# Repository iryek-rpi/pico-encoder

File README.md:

# TCP/IP packet encoder based on Raspberry Pi Pico W + W5500-EVB-Pico

* Raspberry Pi Pico W for serving a device configuration web page
* W5500-EVB-Pico from Wiznet for TCP/IP relay

## Sponsorship from PCBWay

* [PCBWay](https://www.pcbway.com/) kindly provided PCB of this device. This is my first time using the company's service.
* My honest impression is that their service is **well-streamlined with web-based ordering process** with good support of **instant chat assistance**. I could quickly make my order on the comprehensive web page.
* It took about a week to receive the assembled PCB at home in Korea. It was good to see that **each PCB was separately packaged**. The quality of the final product was excellent.
* I want to thank PCBWay again for their support. Highly recommend PCBWay. Try their excellent service at https://www.pcbway.com/ .

### Package arrived!
  * 
  * 
  * 

### KiCad schematics & pcb
  * 
  * 
### FreeCAD design & enclosure
  * 
  * 
  *

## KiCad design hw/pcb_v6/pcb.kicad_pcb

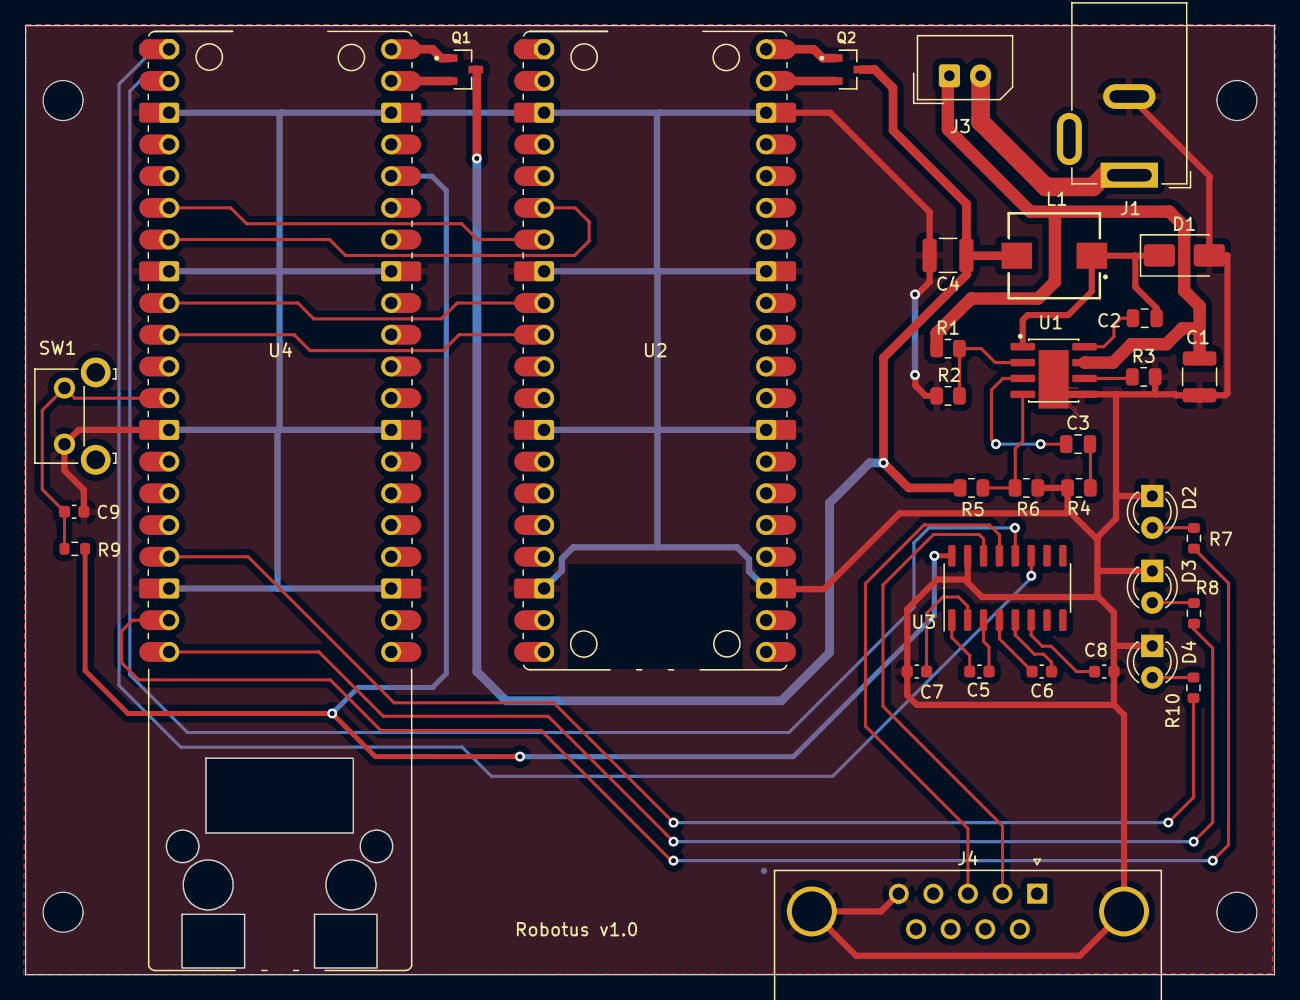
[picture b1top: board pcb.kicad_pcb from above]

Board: 2 copper layers, 100.0 x 76.0 mm, 34 parts (0 on the bottom side), 37 nets.

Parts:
C1: 10uF 50V; C_1210_3225Metric
C2: 0.1uF; C_0805_2012Metric
C3: 220pF; C_0805_2012Metric
C4: 22uF; C_1210_3225Metric
C5, C6, C7, C8: 100nF; C_0603_1608Metric
C9: 10nF; C_0603_1608Metric
D1: SS34; D_SMA
D2, D3, D4: LED; LED_D3.0mm
J1: Barrel_Jack_MountingPin; BarrelJack_GCT_DCJ200-10-A_Horizontal
J3: Conn_01x02; Molex_SPOX_5267-02A_1x02_P2.50mm_Vertical
J4: RS232; DSUB-9_Female_Horizontal_P2.77x2.84mm_EdgePinOffset7.70mm_H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
L1: 4.7uH; INDP7368X320_Inductor
Q1, Q2: DMG2305UX-7; SOT91P240X110-3N_DMG2305UX-7
R1: 100K; R_0805_2012Metric
R2: 24K9; R_0805_2012Metric
R3: 200K; R_0805_2012Metric
R4: 68K; R_0805_2012Metric
R5: 43K; R_0805_2012Metric
R6: 8K2; R_0805_2012Metric
R7, R8, R10: 120; R_0603_1608Metric
R9: 1K; R_0603_1608Metric
SW1: SW_Push; SW_SPST_Omron_B3F-315x_Angled
U1: MP1584EN; SOIC127P600X170-9N_MP1584EN
U2: Raspberry Pi Pico W; Raspberry_Pi_Pico_W_SMT_THT
U3: MAX3232; SO-16_3.9x9.9mm_P1.27mm
U4: W5500-EVB-Pico; W5500-EVB-Pico_SMT_THT

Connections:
+3.3V: R9.1, U3.16 (VCC), U4.36 (3V3)
+5V: C4.1, L1.2, Q1.3, Q2.3, R5.1
+24V: C1.1, J3.1, R1.1, U1.7 (VIN)
+24VP: J1.1, J3.2
BTN: C9.1, R9.2, SW1.2, U4.12 (GPIO9)
GND: C1.2, C4.2, C7.2, C8.2, C9.2, D1.2, D2.1 (K), D3.1 (K), D4.1 (K), J1.2, J4.0 (PAD), J4.5, R2.2, R3.2, R4.2, R6.2, SW1.1, U1.5 (GND), U2.3 (GND_1), U2.8 (GND_2), U2.13 (GND_3), U2.18 (GND_4), U2.23 (GND_5), U2.28 (GND_6), U2.33 (AGND), U2.38 (GND_7), U3.15 (GND), U4.3 (GND_1), U4.8 (GND_2), U4.13 (GND_3), U4.18 (GND_4), U4.23 (GND_5), U4.28 (GND_6), U4.33 (AGND), U4.38 (GND_7)
unnamed: C3.2, R4.1
unnamed: D2.2 (A), R7.1
unnamed: D3.2 (A), R8.1
unnamed: D4.2 (A), R10.1
unnamed: C2.1, U1.8 (BST)
unnamed: C3.1, U1.3 (COMP)
unnamed: R1.2, R2.1, U1.2 (EN)
unnamed: R5.2, R6.1, U1.4 (FB)
unnamed: R3.1, U1.6 (FREQ)
unnamed: C2.2, L1.1, U1.1 (SW)
unnamed: Q2.1, U2.40 (VBUS)
unnamed: Q2.2, U2.39 (VSYS)
unnamed: C5.1, U3.1 (C1+)
unnamed: C5.2, U3.3 (C1-)
unnamed: C6.1, U3.4 (C2+)
unnamed: C6.2, U3.5 (C2-)
unnamed: C7.1, U3.2 (VS+)
unnamed: C8.1, U3.6 (VS-)
unnamed: R10.2, U4.17 (GPIO13)
unnamed: R7.2, U4.19 (GPIO14)
unnamed: R8.2, U4.20 (GPIO15)
unnamed: Q1.1, U4.40 (VBUS)
unnamed: Q1.2, U4.39 (VSYS)
P6: U2.9 (GPIO6), U4.9 (GPIO6)
P7: U2.10 (GPIO7), U4.10 (GPIO7)
RS232_RX: J4.3, U3.13 (R1IN)
RS232_TX: J4.2, U3.14 (T1OUT)
UART0_RX: U3.12 (R1OUT), U4.2 (GPIO1)
UART0_TX: U3.11 (T1IN), U4.1 (GPIO0)
UART1_RX: U2.6 (GPIO4), U4.7 (GPIO5)
UART1_TX: U2.7 (GPIO5), U4.6 (GPIO4)

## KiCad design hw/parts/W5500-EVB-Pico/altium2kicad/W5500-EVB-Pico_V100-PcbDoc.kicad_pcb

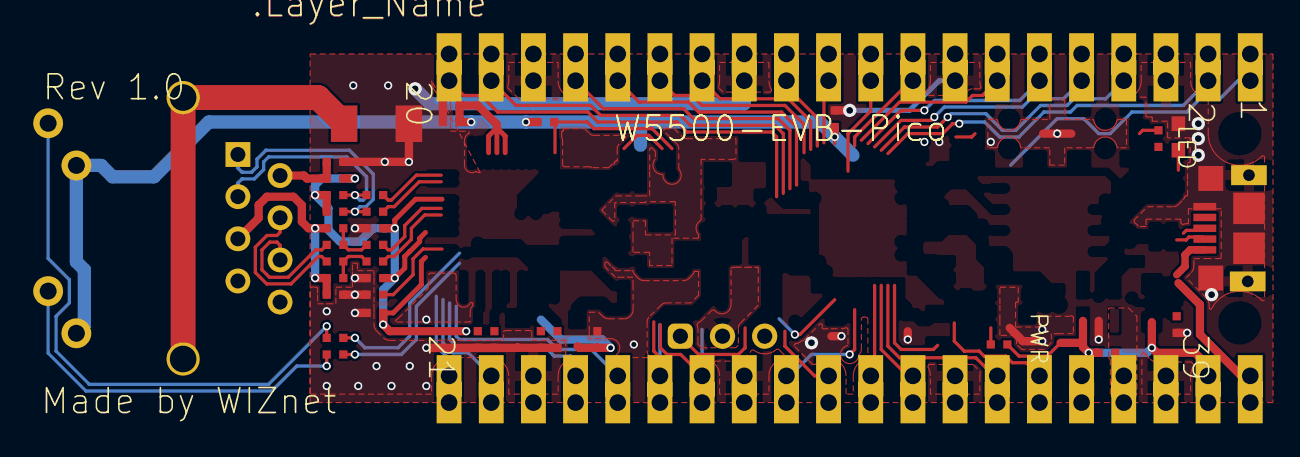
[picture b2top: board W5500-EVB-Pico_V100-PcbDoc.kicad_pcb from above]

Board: 2 copper layers, 39 parts (0 on the bottom side), 18 nets.

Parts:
C12, C15, C16, C17, C18, C19, C20, C21, C22, C23, C28, C29, C30, C35, C36: Ceramic CAP 0402(1005); CAP-0402
C31: Ceramic CAP 1808(4520); CAP-1808
J1, J2: 2.54mm 1x20 Pin Header DIP; IDC-1X20
J3: 2.54mm 1x3 Pin Header DIP; IDC-1X3
LD2: LED-0603; LED-0603-GREEN
P1: Micro USB B Connector SMD; MICRO 5P B DBX 6.4
P2: J1B1211CCD; RJ45-J1B1211CCD
R3, R4, R5, R12, R15, R16, R17, R18, R19, R20, R21, R22, R26, R27, R28, R29, R30: RES-0402

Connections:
3V3: C12.2, C15.2, C16.2, J2.16, P2.10, P2.12, R12.2
3V3A: C17.2, C18.2, C19.2, C20.2, C21.2, C22.2, C23.2, R19.2, R20.2, R28.1
3V3_EN: J2.17, R3.2
CHGND: C31.2, P2.S1, P2.S2
GND: C12.1, C15.1, C16.1, C17.1, C18.1, C19.1, C20.1, C21.1, C22.1, C23.1, C28.1, C29.1, C30.1, C31.1, J1.3, J1.8, J1.13, J1.18, J2.3, J2.8, J2.13, J2.18, J3.2, LD2.2, P1.5, P1.6, P1.7, P1.8, P1.9, P1.10, P1.11, R4.1, R27.2
GPIO20: J2.6, R12.1
NetC28_2: C28.2, P2.2, R28.2
NetC30_2: C30.2, P2.5, R21.1, R22.1
NetC35_1: C35.1, R18.1, R22.2
NetC35_2: C35.2, P2.4
NetC36_1: C36.1, R17.1, R21.2
NetC36_2: C36.2, P2.6
NetP2_1: P2.1, R16.1, R19.1
NetP2_3: P2.3, R15.1, R20.1
NetP2_9: P2.9, R29.1
NetP2_11: P2.11, R30.1
VBUS: J2.20, P1.1
VSYS: J2.19, R3.1, R5.2

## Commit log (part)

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2023-03-29 schematic v1 completed
2023-04-14 old pcb backups removed
2023-04-14 add pcbbackup/*.zip
2023-04-14 datasheets of parts used in JLCPCB 1st order
2023-04-14 bom xml for JLCPCB 1st order
2023-04-16 serial data example
2023-04-16 pico-w files
2023-04-16 backup ex files
2023-04-16 back up examples
2023-04-16 moved to memo folder
2023-04-17 저항 변경
2023-04-17 common read/write main.py for pico-w
2023-04-17 socket server client examples
2023-04-17 encryption
2023-04-17 w5500 successful receive / send
2023-04-25 case base for fitting pcb into the design
2023-04-25 latest kicad project files
2023-04-26 2023.4 최신 회로 및 PCB
2023-04-26 move to sw_pcbv1
2023-04-26 software for pcb v2
2023-04-27 json 예제
2023-04-27 setting
2023-04-28 uart1 settings exchange
2023-04-28 소자 이름 깨지는 거 수정
2023-04-28 소자 파일 이름 깨지는 문제 수정
2023-04-29 pico-w micropython release v1.20.0 2023.04.26
2023-04-29 None to 'N' in json
2023-04-29 main.py update
2023-04-29 phew example
2023-04-30 backup phew apis
2023-04-30 settings based on phewap
2023-05-06 firmwares
2023-05-06 example tcp code
2023-05-06 code for pcb v2
2023-05-06 new case design
2023-05-06 old pcb removed
2023-05-06 old pcb folder renamed
2023-05-06 2023.4 delivery from interboard
2023-05-06 pcb v6 a new copy for three LEDs
2023-05-06 refactor
2023-05-06 add comment
2023-05-06 sch update
2023-05-07 pcb update
2023-05-07 pcb backups
2023-05-07 power ic MP1584EN library footprint update
2023-05-07 sch & pcb update
2023-05-08 gerber sent to jlcpcb
2023-05-08 create spreadsheet
2023-05-08 freecad pcb + w550 + db9
2023-05-09 free cad case design
2023-05-10 rocker sw 10x15 datasheet
2023-05-10 base sheet finished
2023-05-10 freecad backup
2023-05-11 latest
2023-05-11 export to dxf for test
2023-05-13 din rail data
2023-05-13 din rail holes, tech draw pages
2023-05-14 right view dxf
2023-05-14 dxf update
2023-05-14 font for silk printing
2023-05-14 design for printing
2023-05-14 hole for push button
2023-05-14 silk design
2023-05-14 freecad update
2023-05-14 dxf files
2023-05-14 device mart 주문
2023-05-17 add case image and schematics
2023-05-21 Update README.md with schematics
2023-05-21 add images
2023-05-21 rename pcb.jpg
2023-05-21 Update README.md with more images
2023-05-24 led 테스트 코드
2023-05-24 최신 회로도 pdf
2023-05-25 3차 케이스 의뢰
2023-05-29 case USB1 -> USB11 변경
2023-06-04 5.26 case order update
2023-06-06 pico-w 제거용 소스
2023-06-06 usb cover
2023-06-06 usb cover stl
2023-06-06 w5500 main
2023-06-08 LED api update
2023-06-08 w5500 초기화 함수 수정
2023-06-08 LED update & W5500 ip assign update
2023-06-11 old main backup
2023-06-11 led update
2023-06-11 settings.json
2023-06-11 w5500 update
2023-06-11 latest main.py
2023-06-12 mpyaes
2023-06-13 AES encode/decode API
2023-06-13 process encode, decode call via socket
2023-06-13 v1.0
2023-06-14 asyncio uart 예제 코드
2023-06-14 async socket examples
2023-06-14 use poll to unblock socket.accept() & socket.recv()
2023-06-18 w5500 async
2023-06-18 add PC program for KC test
2023-06-18 config for KC test program
2023-06-18 w5500 echo and loopback example
2023-06-18 async start_server 예제
2023-06-18 asyncio start_server 실험
2023-06-28 CTKMessagebox 제거
2023-06-28 baud=9600, w5500_init() 리턴값 처리, 사용하지 않는 함수 삭제
2023-06-28 refactoring LED.py
2023-06-28 w5500_init() returns NULL on failure
2023-06-28 refactoring
2023-06-28 ip 할당 실패 시 시리얼 서버만 실행
2023-06-28 kc인증 테스트 프로그램 매뉴얼 폴더
2023-06-28 프로그램 시작 시 dhcp event 처리, 프로그램 버전 표시
2023-06-28 /tty/USB0 -> COM7
2023-06-28 pyinstaller command
2023-06-28 단계별 실행 방법 추가
2023-06-29 단말에서 읽어온 설정을 UI에 적용 시 문제점 수정 중
2023-06-29 async 예제
2023-07-01 async socket 구현을 위한 코드
2023-07-01 w5500 모듈에 맞게 UART 변경, uart readline()을 위해 \n 추가
2023-07-01 pyb의 heartbeat()을 w5500 모듈에 맞게 수정
2023-07-01 uart async 예제코드
2023-07-03 w5500-evb-pico 회로도 pdf
2023-07-03 KC인증 ESD 이슈 대응을 위한 w5500-evb-pico PCB, 회로도 캡쳐
2023-07-03 KC 인증 시험 1차 소스
2023-07-03 w5500-evb-pico ESD protection capacitor 사진
2023-07-08 성능 인증용 델파이 클라이언트 프로젝트
2023-07-09 serial 예제 수정
2023-10-16 ture -> true
2023-10-16 option 추가, ui layout, options 별도 파일로 변경
2023-10-17 add pico_net_init()
2023-10-17 add LED functions
2023-10-17 variable name refactoring
2023-10-17 make a new function for fix key length and encode the key
2023-10-17 gather code into garbage_collect()
2023-10-17 add pico_init_socket()
2023-10-18 remove unused variables, do_serial() -> process_serial_msg()
2023-10-18 refactor run_hybrid_server()
2023-10-18 backup w5500 code used at RAPA
2023-10-18 move unused w5500 code to backup
2023-10-18 correct default settings to include all fields
2023-10-18 print memory in garbage_collect(), keyb -> fixed_binary_key
2023-10-18 serial_thread_running -> global_run_flag
2023-10-18 PC 클라이언트 백업 epc -> epc_2023.10.19
2023-10-18 add CHANNEL to default settings
2023-10-18 run_hybrid_server(settings, uart) argument changed
2023-10-18 New source tree to include PC client and W5500 code
2023-10-18 refactor main.py
2023-10-18 add a folder for w5500 socket examples
2023-10-19 socket 예제 수정
2023-10-19 realpython socket programming examples
2023-10-19 socket blocking test code
2023-10-19 creypto port added to settings
2023-10-19 register 4 sockets to poll()
2023-10-20 move ex/ -> sw/ex/
2023-10-20 move web/ -> sw/web/
2023-10-20 sw/ex/phewap -> sw/ex/web/phewap
2023-10-20 move web examples to sw/ex/web/
2023-10-20 add micropyserver example
2023-10-20 correct error
2023-10-20 add phew files
2023-10-20 add config_web.py for phew
2023-10-20 convert main_single() to async
2023-10-20 async await 예제 추가
2023-10-21 add find_host_ip()
2023-10-21 serial로 암호화 요청 실패하는 소스
2023-10-29 flet example from youtube
2023-11-07 make window smaller
2023-11-07 조립 시 테스트 코드
2023-11-07 11월8일 플래싱 10대 MicroPython 펌웨어
2023-11-08 led_state_good() turns on RED
2023-11-08 init_serial() to accept parameters
2023-11-08 use sleep_ms()
2023-11-08 add definitions
2023-11-08 refactor init_server_sockets() to seperate text & crypto port initialization
2023-11-09 설정에 따라 필요할 때만 text port 트래픽 확인
2023-11-09 use settings[] instead of making variables
2023-11-10 CHANNEL definition change
2023-11-10 change async functions to sync
2023-11-10 tcp socket receive fix
2023-11-10 README for package list backup & restore for environment
2023-11-10 clear_button -> start_server_button
2023-11-10 backup package list
2023-11-10 remove DHCP
2023-11-10 refactor device_options.py
2023-11-11 flet entry_form example
2023-11-11 tcl/tk async example
2023-11-11 epc async server 시도
2023-11-11 Flet based test program
2023-11-11 flet UI code implementation
2023-11-11 make async process_serial_msg a sync function
2023-11-11 garbage_collect(), init_serial() refactoring
2023-11-11 move garbage_collect() to utils.py
2023-11-11 change order of parameters for init_serial(N,8,1)
2023-11-11 move w5x00_init() to pico_net.py
2023-11-11 remove global_run_flag
2023-11-11 remove main_single(), make run_hybrid_server() async
2023-11-12 update html
2023-11-12 update html & valication
2023-11-12 config mode
2023-11-12 tcp server
2023-11-13 asyncio stream example
2023-11-14 socket stream example ok
2023-11-14 MicroPython 최신 펌웨어에 Wiznet TCP/IP 스택 올린 펌웨어(2023.10.12)
2023-11-14 load_settings and refactoring
2023-11-14 json settings refactoring
2023-11-14 json ex
2023-11-20 channel에 따라 serial, tcp 처리
2023-11-21 add constans.py for constant definition
2023-11-22 html examples
2023-11-22 stream read write
2023-11-22 move crypto functions to coder.py
2023-11-22 refactor stream handlers
2023-11-24 main.py -> main_old.py
2023-11-24 main_w5500.py -> main.py
2023-11-25 refactor serial settings argument
2023-11-25 w5500 stream example code
2023-11-25 use blocking socket for send() inside stream handler
2023-11-25 stream example
2023-11-25 list serial port example
2023-11-25 do not use prefix and suffix from TCP message
2023-11-29 send data in sync via serial or tcp
2023-11-29 use settings[utils.CHANNEL]
2023-12-02 add images for logo
2023-12-02 remove debug messages
2023-12-02 add latest firmware from MicroPython.org
2023-12-02 add files for favicon but not working yet
2023-12-02 fix quotation marks around string inside string
2023-12-02 hardware changes
2023-12-02 change debug messages
2023-12-02 fix bugs
2023-12-02 입력데이터 없을 때, 에러 다이알로그
2023-12-02 use decoded text to extract msg from serial data due to \n in the data
2023-12-02 start both serial and tcp server. put serial init exception to history
2023-12-02 add catchall handler for 404 Not Found
2023-12-02 use port 2004 for TEXT server
2023-12-02 remove device port input field
2023-12-02 remove comment
2023-12-02 change tcp server not to close connection
2023-12-03 web setting & validation
2023-12-04 create async_relay docker images
2023-12-04 device to device socket read/write
2023-12-04 update relay
2023-12-04 rm k2_config.txt
2023-12-04 implement relay
2023-12-04 move sw/ex/async_docker -> sw/docker
2023-12-04 for client, server
2023-12-04 fix relay function
2023-12-06 organize example files
2023-12-06 fix serial client/server examples
2023-12-06 on fixing serial handler to add relay function
2023-12-07 add relay function for serial msg
2023-12-07 fix error
2023-12-07 move constants in utils.py to contants.py
2023-12-07 move constants in utils.py to constants.py
2023-12-07 OptionRow, OptionGroup
2023-12-07 Use of OptionRow, OptionGroup
2023-12-07 add control_reference.py
2023-12-07 remove backups
2023-12-07 fix a bug
2023-12-07 move constants from utils.py to constants.py
2023-12-08 moved constants from utils.py to contants.py
2023-12-08 settings -> g_settings for global variable
2023-12-08 simulate serial msg relay on docker device image
2023-12-08 asyncio stream client/server example
2023-12-08 serial client/server update
2023-12-08 define sleep 30ms, 50ms
2023-12-08 encrypt/decrypt debug messages
2023-12-08 serial channel ok
2023-12-08 update tcp client/server
2023-12-10 decryption test client
2023-12-11 list serial port
2023-12-11 flet UI
2023-12-11 test client
2023-12-11 Zudohari test client and device server
2023-12-12 pc option file 구현 준비
2023-12-12 move DEFAULT_SETTINGS from utils to constants
2023-12-12 use OS class for OptionStore
2023-12-12 config mode 삭제
2023-12-12 OS.apply_settings()
2023-12-12 add pc_settings.json
2023-12-13 fix a logic error and wrong key names in web settings
2023-12-16 html example by AI
2023-12-16 index.html update with AI suggestions
2023-12-17 read mac and save, sample mac.bin
2023-12-17 device #11, #12 and update w5500.py
2023-12-17 rename
2023-12-17 index.html re-design
2023-12-17 MAX_MSG = 1500
2023-12-17 device id & use global settings for web
2023-12-17 remove config when saving from web
2023-12-17 button to default settings
2023-12-17 <16자
2023-12-18 color scheme suggestion by bard
2023-12-18 index.html color scheme chaged
2023-12-18 remove unused files
2023-12-18 #id, 4~16자
2023-12-18 main() saves mac and verify
2023-12-18 타이틀에 '설정' 삭제
2023-12-18 change default setting values
2023-12-18 mac script
2023-12-18 mac for device 2~6
2023-12-18 remove all mac information
2023-12-19 get_mac.py
2023-12-19 call led_state_reset() before reset
2023-12-19 call led_state_reset() before reset, refactor comments
2023-12-19 led state for error cases
2023-12-19 led_state_data_error()
2023-12-19 assign IP on connecting lan cable
2023-12-20 refactor logging
2023-12-20 flet change bgcolor of dropdowni by using Containerw
2023-12-20 flet dropdown example
2024-01-03 implementing crypto api server
2024-08-13 경율이 xor 암호화
2024-08-26 refactor & test
2024-08-26 back up sw from delivered device
2024-08-26 경율 xor encoding/decoding 적용
2024-10-23 socket client/server examples
2024-10-23 xor test code
2024-10-23 host port = 2004
2024-10-23 Release only modified files for xor
2024-10-23 released zip file
2024-11-10 prevent OSError: [Errno 98] Address already in use
2024-11-10 fix peer port
2024-11-10 add release 2024.11.11
2024-11-10 2024.11.11 backup XOR with key & without key OK!!!
2024-12-09 remove xor from main branch
2024-12-09 threaded client, server example
2024-12-09 switch handle_crypto/text, reset on error, catch exception on stream read/write
2024-12-09 catch exception from wrtier.write
2024-12-09 fix serial handler apply
2024-12-10 revise comment
2024-12-10 chagne port names in order to avoid confusion
2024-12-10 uasyncio socket example
2024-12-10 remove exception handling
2024-12-10 implementing chat (not finished)
